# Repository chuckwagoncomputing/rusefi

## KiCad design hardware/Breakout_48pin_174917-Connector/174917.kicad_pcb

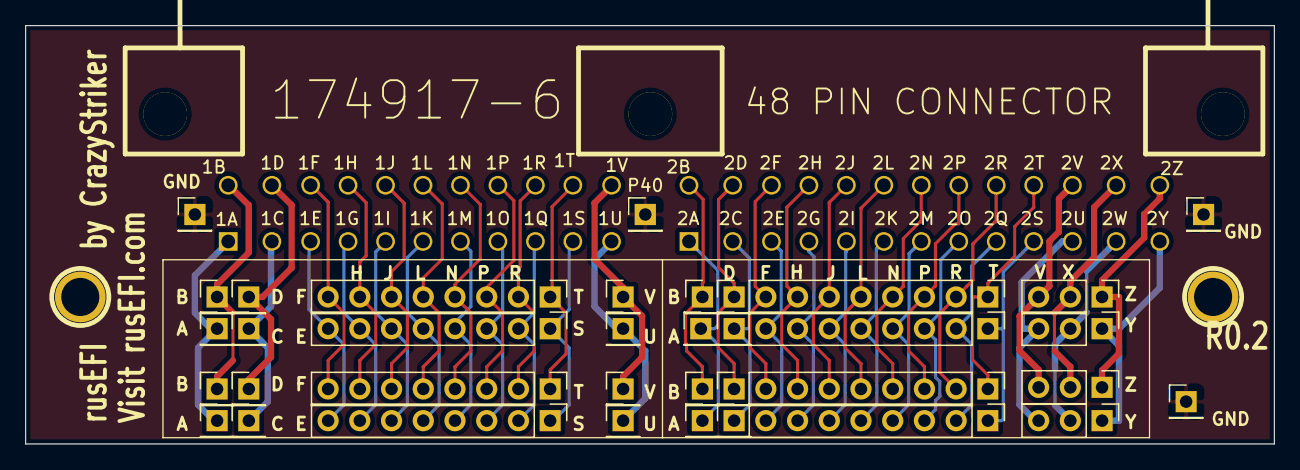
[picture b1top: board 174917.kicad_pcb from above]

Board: 2 copper layers, 100.0 x 33.5 mm, 39 parts (0 on the bottom side), 49 nets.

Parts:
1PIN, 1PIN#2: P***; 1pin
P1, P2, P13, P14: CONN_3; PinHeader_1x03_P2.54mm_Vertical
P3, P4, P5, P6, P7, P8, P9, P10, P11, P12, P15, P16, P17, P18, P19, P20, P21, P22, P23, P24, P38, P39, P40, P41: CONN_1; PinHeader_1x01_P2.54mm_Vertical
P25: 174917
P26, P27, P30, P31, P32, P33, P36, P37: CONN_8; PinHeader_1x08_P2.54mm_Vertical

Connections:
GND: P38.1, P39.1, P40.1, P41.1
unnamed: P1.1, P13.1
unnamed: P1.2, P13.2
unnamed: P1.3, P13.3
unnamed: P10.1, P22.1
unnamed: P11.1, P23.1
unnamed: P12.1, P24.1
unnamed: P2.1, P14.1
unnamed: P2.2, P14.2
unnamed: P2.3, P14.3
unnamed: P3.1, P15.1
unnamed: P4.1, P16.1
unnamed: P5.1, P17.1
unnamed: P6.1, P18.1
unnamed: P7.1, P19.1
unnamed: P8.1, P20.1
unnamed: P9.1, P21.1
unnamed: P26.1, P32.1
unnamed: P26.3, P32.3
unnamed: P26.4, P32.4
unnamed: P26.5, P32.5
unnamed: P26.6, P32.6
unnamed: P26.7, P32.7
unnamed: P26.8, P32.8
unnamed: P27.1, P33.1
unnamed: P27.2, P33.2
unnamed: P27.3, P33.3
unnamed: P27.4, P33.4
unnamed: P27.5, P33.5
unnamed: P27.6, P33.6
unnamed: P27.7, P33.7
unnamed: P27.8, P33.8
unnamed: P30.1, P36.1
unnamed: P30.2, P36.2
unnamed: P30.3, P36.3
unnamed: P30.4, P36.4
unnamed: P30.5, P36.5
unnamed: P30.6, P36.6
unnamed: P30.7, P36.7
unnamed: P30.8, P36.8
unnamed: P31.1, P37.1
unnamed: P31.2, P37.2
unnamed: P31.3, P37.3
unnamed: P31.4, P37.4
unnamed: P31.5, P37.5
unnamed: P31.6, P37.6
unnamed: P31.7, P37.7
unnamed: P31.8, P37.8
unnamed: P26.2, P32.2

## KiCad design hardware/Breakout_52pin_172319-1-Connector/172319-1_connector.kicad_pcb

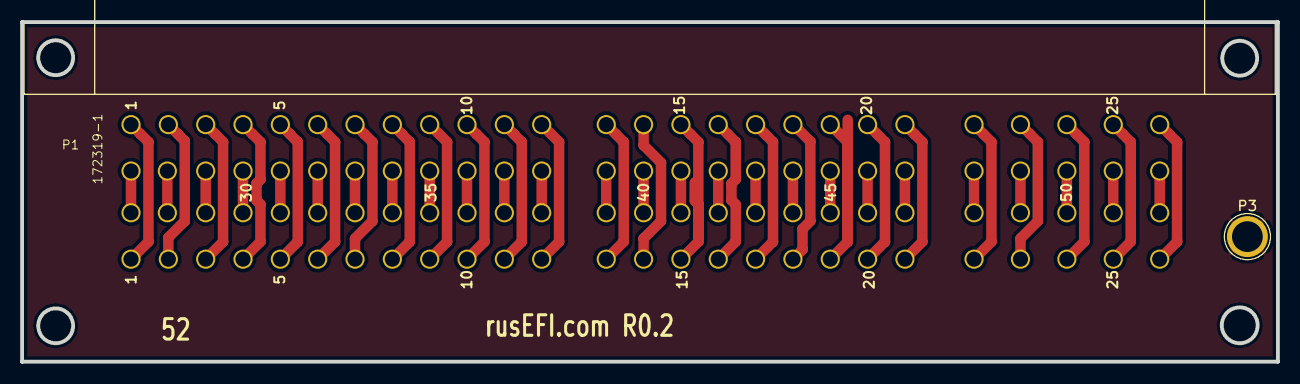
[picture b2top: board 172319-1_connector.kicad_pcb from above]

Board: 2 copper layers, 124.5 x 33.7 mm, 3 parts (1 on the bottom side), 52 nets.

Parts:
P1, P2: 172319-1; 172319-1_connector
P3: CONN_01X01; 1pin

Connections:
unnamed: P1.1, P2.1
unnamed: P1.2, P2.2
unnamed: P1.3, P2.3
unnamed: P1.4, P2.4
unnamed: P1.5, P2.5
unnamed: P1.6, P2.6
unnamed: P1.7, P2.7
unnamed: P1.8, P2.8
unnamed: P1.9, P2.9
unnamed: P1.10, P2.10
unnamed: P1.11, P2.11
unnamed: P1.12, P2.12
unnamed: P1.13, P2.13
unnamed: P1.14, P2.14
unnamed: P1.15, P2.15
unnamed: P1.16, P2.16
unnamed: P1.17, P2.17
unnamed: P1.18, P2.18
unnamed: P1.19, P2.19
unnamed: P1.20, P2.20
unnamed: P1.21, P2.21
unnamed: P1.22, P2.22
unnamed: P1.23, P2.23
unnamed: P1.24, P2.24
unnamed: P1.25, P2.25
unnamed: P1.26, P2.26
unnamed: P1.27, P2.27
unnamed: P1.28, P2.28
unnamed: P1.29, P2.29
unnamed: P1.30, P2.30
unnamed: P1.31, P2.31
unnamed: P1.32, P2.32
unnamed: P1.33, P2.33
unnamed: P1.34, P2.34
unnamed: P1.35, P2.35
unnamed: P1.36, P2.36
unnamed: P1.37, P2.37
unnamed: P1.38, P2.38
unnamed: P1.39, P2.39
unnamed: P1.40, P2.40
unnamed: P1.41, P2.41
unnamed: P1.42, P2.42
unnamed: P1.43, P2.43
unnamed: P1.44, P2.44
unnamed: P1.45, P2.45
unnamed: P1.46, P2.46
unnamed: P1.47, P2.47
unnamed: P1.48, P2.48
unnamed: P1.49, P2.49
unnamed: P1.50, P2.50
unnamed: P1.51, P2.51
unnamed: P1.52, P2.52

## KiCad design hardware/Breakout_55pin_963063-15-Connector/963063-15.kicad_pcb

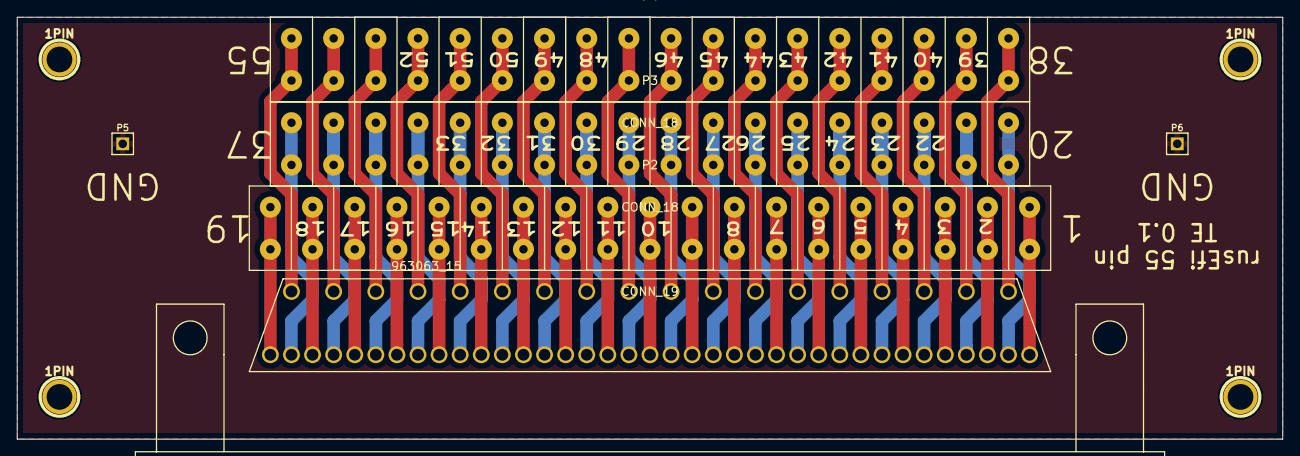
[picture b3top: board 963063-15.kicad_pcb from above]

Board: 2 copper layers, 150.0 x 50.0 mm, 10 parts (0 on the bottom side), 56 nets.

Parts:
1PIN, 1PIN#2, 1PIN#3, 1PIN#4: P***; 1pin
P1: 963063_15; 963063-15
P2: CONN_19; CON19X5
P3, P4: CONN_18; CON18X5
P5, P6: CONN_1; PIN_ARRAY_1

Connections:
GND: P5.1, P6.1
unnamed: P1.11, P2.11
unnamed: P1.1, P2.1
unnamed: P1.2, P2.2
unnamed: P1.3, P2.3
unnamed: P1.4, P2.4
unnamed: P1.5, P2.5
unnamed: P1.6, P2.6
unnamed: P1.7, P2.7
unnamed: P1.8, P2.8
unnamed: P1.9, P2.9
unnamed: P1.10, P2.10
unnamed: P1.55, P4.18
unnamed: P1.12, P2.12
unnamed: P1.13, P2.13
unnamed: P1.14, P2.14
unnamed: P1.15, P2.15
unnamed: P1.16, P2.16
unnamed: P1.17, P2.17
unnamed: P1.18, P2.18
unnamed: P1.19, P2.19
unnamed: P1.20, P3.1
unnamed: P1.21, P3.2
unnamed: P1.44, P4.7
unnamed: P1.34, P3.15
unnamed: P1.35, P3.16
unnamed: P1.36, P3.17
unnamed: P1.37, P3.18
unnamed: P1.38, P4.1
unnamed: P1.39, P4.2
unnamed: P1.40, P4.3
unnamed: P1.41, P4.4
unnamed: P1.42, P4.5
unnamed: P1.43, P4.6
unnamed: P1.22, P3.3
unnamed: P1.45, P4.8
unnamed: P1.46, P4.9
unnamed: P1.47, P4.10
unnamed: P1.48, P4.11
unnamed: P1.49, P4.12
unnamed: P1.50, P4.13
unnamed: P1.51, P4.14
unnamed: P1.52, P4.15
unnamed: P1.53, P4.16
unnamed: P1.54, P4.17
unnamed: P1.33, P3.14
unnamed: P1.23, P3.4
unnamed: P1.24, P3.5
unnamed: P1.25, P3.6
unnamed: P1.26, P3.7
unnamed: P1.27, P3.8
unnamed: P1.28, P3.9
unnamed: P1.29, P3.10
unnamed: P1.30, P3.11
unnamed: P1.31, P3.12
unnamed: P1.32, P3.13

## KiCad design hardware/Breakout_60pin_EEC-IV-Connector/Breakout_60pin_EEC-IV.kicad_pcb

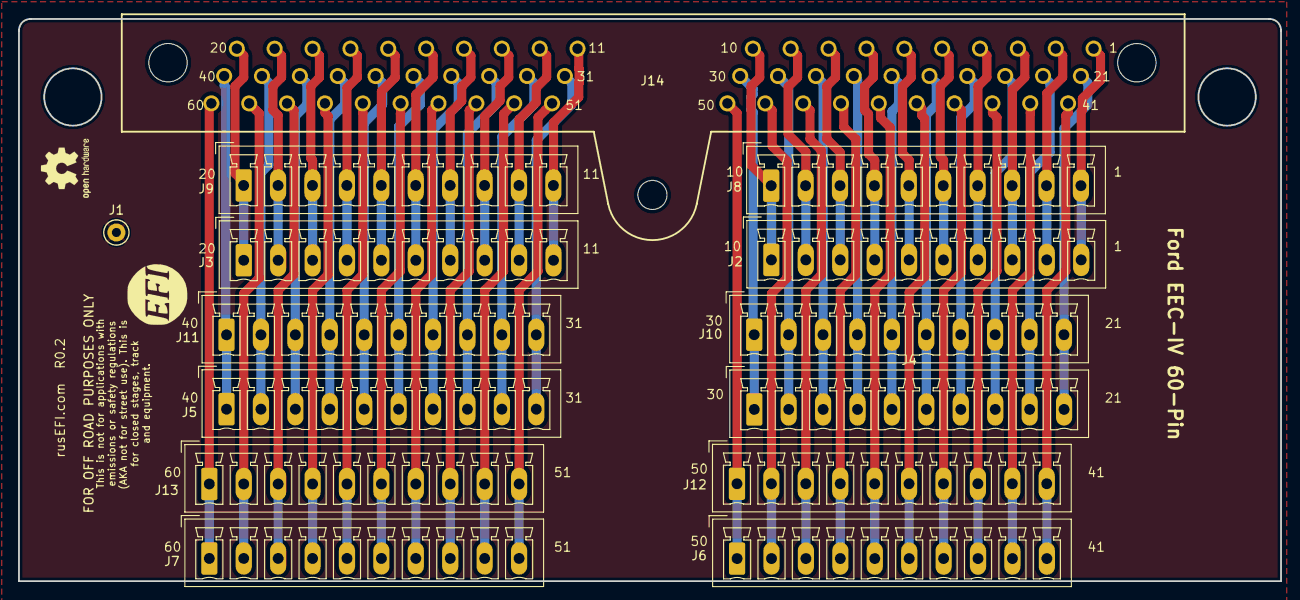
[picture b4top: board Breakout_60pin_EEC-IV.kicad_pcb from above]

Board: 2 copper layers, 139.7 x 62.2 mm, 17 parts (0 on the bottom side), 60 nets.

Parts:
G1: Disclaimer; Off_Road_Disclaimer
G2: LOGO
J1: Conn_01x01; TestPoint_Keystone_5000-5004_Miniature
J2, J3, J4, J5, J6, J7, J8, J9, J10, J11, J12, J13: Conn_01x10; PhoenixContact_MCV_1,5_10-G-3.81_1x10_P3.81mm_Vertical
J14: EEC-IV; eeciv
LOGO1: DNP; OSHW-Logo2_7.3x6mm_SilkScreen

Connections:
/1: J2.10, J8.10, J14.1
/5: J2.6, J8.6, J14.5
/10: J2.1, J8.1, J14.10
/11: J3.10, J9.10, J14.11
/15: J3.6, J9.6, J14.15
/25: J4.6, J10.6, J14.25
/30: J4.1, J10.1, J14.30
/31: J5.10, J11.10, J14.31
/35: J5.6, J11.6, J14.35
/40: J5.1, J11.1, J14.40
/41: J6.10, J12.10, J14.41
/45: J6.6, J12.6, J14.45
/50: J6.1, J12.1, J14.50
/53: J7.8, J13.8, J14.53
/54: J7.7, J13.7, J14.54
/55: J7.6, J13.6, J14.55
/60: J7.1, J13.1, J14.60
/420: J3.1, J9.1, J14.20
/421: J4.10, J10.10, J14.21
unnamed: J4.2, J10.2, J14.29
unnamed: J4.3, J10.3, J14.28
unnamed: J4.4, J10.4, J14.27
unnamed: J4.5, J10.5, J14.26
unnamed: J4.7, J10.7, J14.24
unnamed: J4.8, J10.8, J14.23
unnamed: J4.9, J10.9, J14.22
unnamed: J5.2, J11.2, J14.39
unnamed: J5.3, J11.3, J14.38
unnamed: J5.4, J11.4, J14.37
unnamed: J5.5, J11.5, J14.36
unnamed: J5.7, J11.7, J14.34
unnamed: J5.8, J11.8, J14.33
unnamed: J5.9, J11.9, J14.32
unnamed: J6.2, J12.2, J14.49
unnamed: J6.3, J12.3, J14.48
unnamed: J6.4, J12.4, J14.47
unnamed: J6.5, J12.5, J14.46
unnamed: J6.7, J12.7, J14.44
unnamed: J6.8, J12.8, J14.43
unnamed: J6.9, J12.9, J14.42
unnamed: J7.2, J13.2, J14.59
unnamed: J7.3, J13.3, J14.58
unnamed: J7.4, J13.4, J14.57
unnamed: J7.5, J13.5, J14.56
unnamed: J7.9, J13.9, J14.52
unnamed: J7.10, J13.10, J14.51
unnamed: J2.9, J8.9, J14.2
unnamed: J2.8, J8.8, J14.3
unnamed: J2.7, J8.7, J14.4
unnamed: J2.5, J8.5, J14.6
unnamed: J2.4, J8.4, J14.7
unnamed: J2.3, J8.3, J14.8
unnamed: J2.2, J8.2, J14.9
unnamed: J3.9, J9.9, J14.12
unnamed: J3.8, J9.8, J14.13
unnamed: J3.7, J9.7, J14.14
unnamed: J3.5, J9.5, J14.16
unnamed: J3.4, J9.4, J14.17
unnamed: J3.3, J9.3, J14.18
unnamed: J3.2, J9.2, J14.19

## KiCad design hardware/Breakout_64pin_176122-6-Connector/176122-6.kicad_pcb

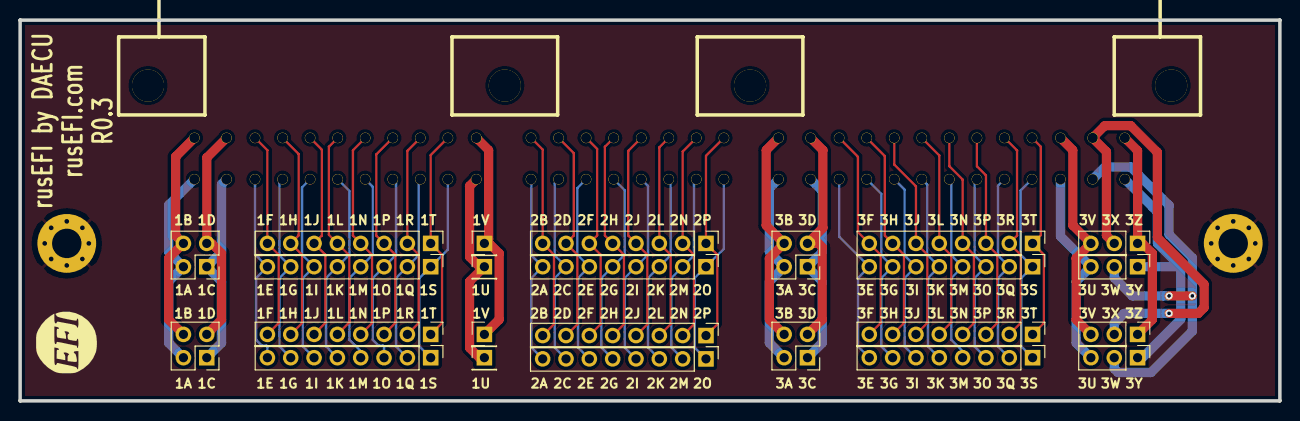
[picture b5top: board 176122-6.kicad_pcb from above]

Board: 2 copper layers, 137.2 x 41.5 mm, 28 parts (0 on the bottom side), 65 nets.

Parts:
G1: LOGO
H1, H2: MountingHole_Pad; MountingHole_3.2mm_M3_Pad_Via
P1, P2, P13, P14: CONN_3; PinHeader_1x03_P2.54mm_Vertical
P3, P4, P42, P43: Conn_01x04_Male; PinHeader_2x02_P2.54mm_Vertical
P7, P8, P19, P20: CONN_1; PinHeader_1x01_P2.54mm_Vertical
P25: 0176122-06; 176122-6
P26, P27, P28, P29, P30, P31, P32, P33, P34, P35, P36, P37: CONN_8; PinHeader_1x08_P2.54mm_Vertical

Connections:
GND: H1.1, H2.1
unnamed: P1.1, P13.1, P25.1
unnamed: P1.2, P13.2, P25.2
unnamed: P1.3, P13.3, P25.3
unnamed: P2.1, P14.1, P25.4
unnamed: P2.2, P14.2, P25.5
unnamed: P2.3, P14.3, P25.6
unnamed: P7.1, P19.1, P25.11
unnamed: P8.1, P20.1, P25.12
unnamed: P3.1, P4.1, P25.7
unnamed: P3.2, P4.2, P25.8
unnamed: P3.3, P4.3, P25.9
unnamed: P3.4, P4.4, P25.10
unnamed: P25.13, P42.1, P43.1
unnamed: P25.14, P42.2, P43.2
unnamed: P25.15, P42.3, P43.3
unnamed: P25.16, P42.4, P43.4
unnamed: P25.17, P26.1, P32.1
unnamed: P25.18, P26.2, P32.2
unnamed: P25.19, P26.3, P32.3
unnamed: P25.20, P26.4, P32.4
unnamed: P25.21, P26.5, P32.5
unnamed: P25.22, P26.6, P32.6
unnamed: P25.23, P26.7, P32.7
unnamed: P25.24, P26.8, P32.8
unnamed: P25.25, P27.1, P33.1
unnamed: P25.26, P27.2, P33.2
unnamed: P25.27, P27.3, P33.3
unnamed: P25.28, P27.4, P33.4
unnamed: P25.29, P27.5, P33.5
unnamed: P25.30, P27.6, P33.6
unnamed: P25.31, P27.7, P33.7
unnamed: P25.32, P27.8, P33.8
unnamed: P25.33, P28.1, P34.1
unnamed: P25.34, P28.2, P34.2
unnamed: P25.35, P28.3, P34.3
unnamed: P25.36, P28.4, P34.4
unnamed: P25.37, P28.5, P34.5
unnamed: P25.38, P28.6, P34.6
unnamed: P25.39, P28.7, P34.7
unnamed: P25.40, P28.8, P34.8
unnamed: P25.41, P29.1, P35.1
unnamed: P25.42, P29.2, P35.2
unnamed: P25.43, P29.3, P35.3
unnamed: P25.44, P29.4, P35.4
unnamed: P25.45, P29.5, P35.5
unnamed: P25.46, P29.6, P35.6
unnamed: P25.47, P29.7, P35.7
unnamed: P25.48, P29.8, P35.8
unnamed: P25.49, P30.1, P36.1
unnamed: P25.50, P30.2, P36.2
unnamed: P25.51, P30.3, P36.3
unnamed: P25.52, P30.4, P36.4
unnamed: P25.53, P30.5, P36.5
unnamed: P25.54, P30.6, P36.6
unnamed: P25.55, P30.7, P36.7
unnamed: P25.56, P30.8, P36.8
unnamed: P25.57, P31.1, P37.1
unnamed: P25.58, P31.2, P37.2
unnamed: P25.59, P31.3, P37.3
unnamed: P25.60, P31.4, P37.4
unnamed: P25.61, P31.5, P37.5
unnamed: P25.62, P31.6, P37.6
unnamed: P25.63, P31.7, P37.7
unnamed: P25.64, P31.8, P37.8

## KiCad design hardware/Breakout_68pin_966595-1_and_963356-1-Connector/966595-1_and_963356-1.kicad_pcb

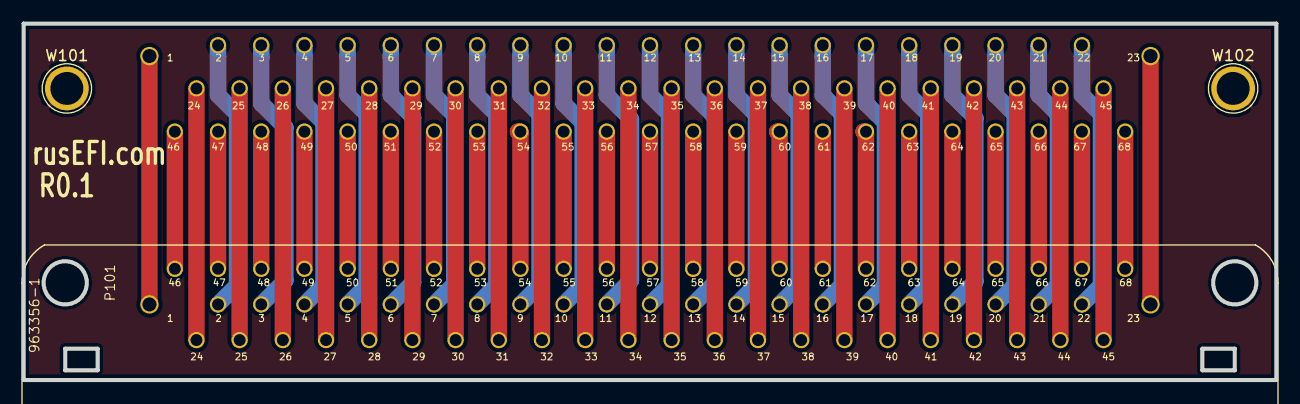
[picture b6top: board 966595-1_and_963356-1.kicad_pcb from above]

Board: 2 copper layers, 116.0 x 33.0 mm, 4 parts (1 on the bottom side), 69 nets.

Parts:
P101: 963356-1
P102: 966595-1
W101, W102: TEST_1P; 1pin

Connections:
GND: W101.1, W102.1
unnamed: P101.1, P102.1
unnamed: P101.2, P102.2
unnamed: P101.3, P102.3
unnamed: P101.4, P102.4
unnamed: P101.5, P102.5
unnamed: P101.6, P102.6
unnamed: P101.7, P102.7
unnamed: P101.8, P102.8
unnamed: P101.9, P102.9
unnamed: P101.10, P102.10
unnamed: P101.11, P102.11
unnamed: P101.12, P102.12
unnamed: P101.13, P102.13
unnamed: P101.14, P102.14
unnamed: P101.15, P102.15
unnamed: P101.16, P102.16
unnamed: P101.17, P102.17
unnamed: P101.18, P102.18
unnamed: P101.19, P102.19
unnamed: P101.20, P102.20
unnamed: P101.21, P102.21
unnamed: P101.22, P102.22
unnamed: P101.23, P102.23
unnamed: P101.24, P102.24
unnamed: P101.25, P102.25
unnamed: P101.26, P102.26
unnamed: P101.27, P102.27
unnamed: P101.28, P102.28
unnamed: P101.29, P102.29
unnamed: P101.30, P102.30
unnamed: P101.31, P102.31
unnamed: P101.32, P102.32
unnamed: P101.33, P102.33
unnamed: P101.34, P102.34
unnamed: P101.35, P102.35
unnamed: P101.36, P102.36
unnamed: P101.37, P102.37
unnamed: P101.38, P102.38
unnamed: P101.39, P102.39
unnamed: P101.40, P102.40
unnamed: P101.41, P102.41
unnamed: P101.42, P102.42
unnamed: P101.43, P102.43
unnamed: P101.44, P102.44
unnamed: P101.45, P102.45
unnamed: P101.46, P102.46
unnamed: P101.47, P102.47
unnamed: P101.48, P102.48
unnamed: P101.49, P102.49
unnamed: P101.50, P102.50
unnamed: P101.51, P102.51
unnamed: P101.52, P102.52
unnamed: P101.53, P102.53
unnamed: P101.54, P102.54
unnamed: P101.55, P102.55
unnamed: P101.56, P102.56
unnamed: P101.57, P102.57
unnamed: P101.58, P102.58
unnamed: P101.59, P102.59
unnamed: P101.60, P102.60
unnamed: P101.61, P102.61
unnamed: P101.62, P102.62
unnamed: P101.63, P102.63
unnamed: P101.64, P102.64
unnamed: P101.65, P102.65
unnamed: P101.66, P102.66
unnamed: P101.67, P102.67
unnamed: P101.68, P102.68

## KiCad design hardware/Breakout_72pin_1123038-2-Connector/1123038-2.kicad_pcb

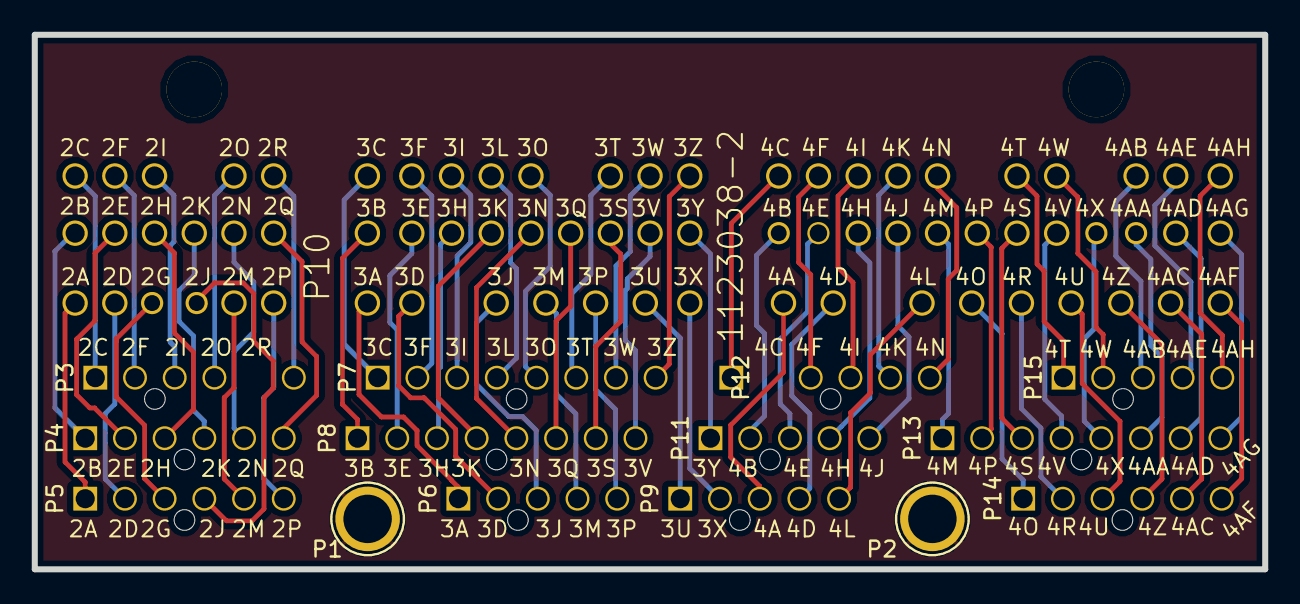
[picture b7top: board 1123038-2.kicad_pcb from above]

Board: 2 copper layers, 77.5 x 33.7 mm, 16 parts (1 on the bottom side), 73 nets.

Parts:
G1: LOGO
P1, P2: CONN_1; 1pin
P3, P6, P9, P11, P12, P15: CONN_01X05; Molex_NanoFit_1x05x2.50mm_Straight
P4, P5, P14: CONN_01X06; Molex_NanoFit_1x06x2.50mm_Straight
P7, P8, P13: CONN_01X08; Molex_NanoFit_1x08x2.50mm_Straight
P10: 1123038-2

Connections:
/2A: P5.1, P10.51
/2B: P4.1, P10.24
/2C: P3.1, P10.1
/2D: P5.2, P10.52
/2E: P4.2, P10.25
/2F: P3.2, P10.2
/2G: P5.3, P10.53
/2H: P4.3, P10.26
/2I: P3.3, P10.3
/2J: P5.4, P10.54
/2K: P4.4, P10.27
/2M: P5.5, P10.55
/2N: P4.5, P10.28
/2P: P5.6, P10.56
/2Q: P4.6, P10.29
/2R: P3.5, P10.5
/3A: P6.1, P10.57
/3B: P8.1, P10.30
/3C: P7.1, P10.6
/3D: P6.2, P10.58
/3E: P8.2, P10.31
/3F: P7.2, P10.7
/3H: P8.3, P10.32
/3I: P7.3, P10.8
/3J: P6.3, P10.59
/3K: P8.4, P10.33
/3L: P7.4, P10.9
/3M: P6.4, P10.60
/3N: P8.5, P10.34
/3O: P7.5, P10.10
/3P: P6.5, P10.61
/3Q: P8.6, P10.35
/3S: P8.7, P10.36
/3T: P7.6, P10.11
/3U: P9.1, P10.62
/3V: P8.8, P10.37
/3W: P7.7, P10.12
/3X: P9.2, P10.63
/3Y: P10.38, P11.1
/3Z: P7.8, P10.13
/4A: P9.3, P10.64
/4AA: P10.48, P13.6
/4AB: P10.21, P15.3
/4AC: P10.71, P14.5
/4AD: P10.49, P13.7
/4AE: P10.22, P15.4
/4AF: P10.72, P14.6
/4AG: P10.50, P13.8
/4AH: P10.23, P15.5
/4B: P10.39, P11.2
/4C: P10.14, P12.1
/4D: P9.4, P10.65
/4E: P10.40, P11.3
/4F: P10.15, P12.2
/4H: P10.41, P11.4
/4I: P10.16, P12.3
/4J: P10.42, P11.5
/4K: P10.17, P12.4
/4L: P9.5, P10.66
/4M: P10.43, P13.1
/4N: P10.18, P12.5
/4O: P10.67, P14.1
/4P: P10.44, P13.2
/4R: P10.68, P14.2
/4S: P10.45, P13.3
/4T: P10.19, P15.1
/4U: P10.69, P14.3
/4V: P10.46, P13.4
/4W: P10.20, P15.2
/4X: P10.47, P13.5
/4Z: P10.70, P14.4
/20: P3.4, P10.4
GND: P1.1, P2.1

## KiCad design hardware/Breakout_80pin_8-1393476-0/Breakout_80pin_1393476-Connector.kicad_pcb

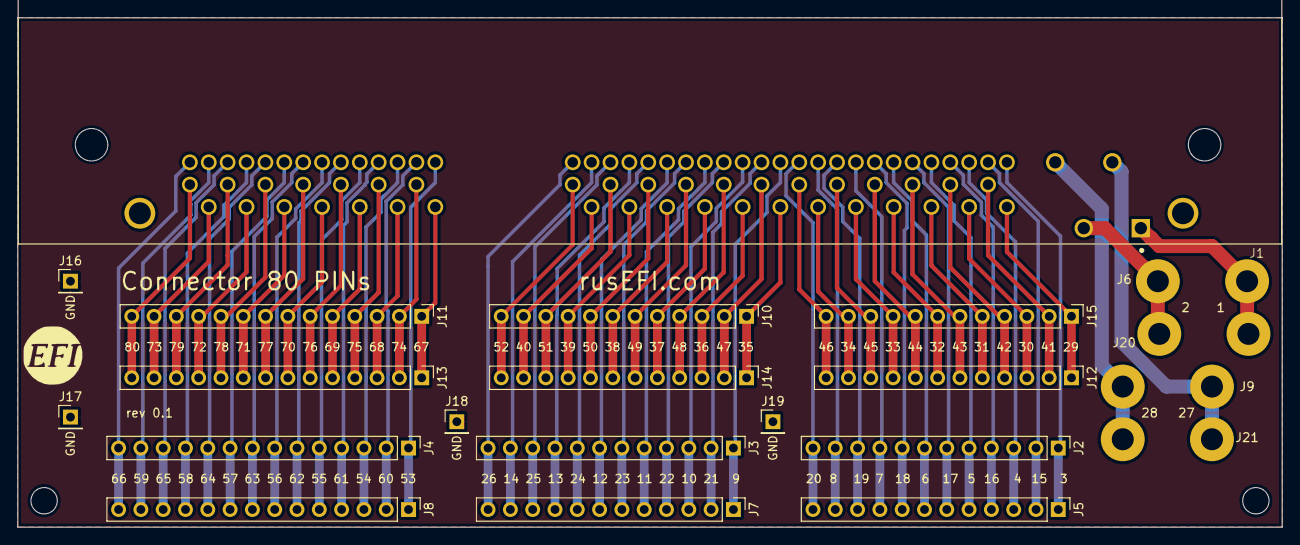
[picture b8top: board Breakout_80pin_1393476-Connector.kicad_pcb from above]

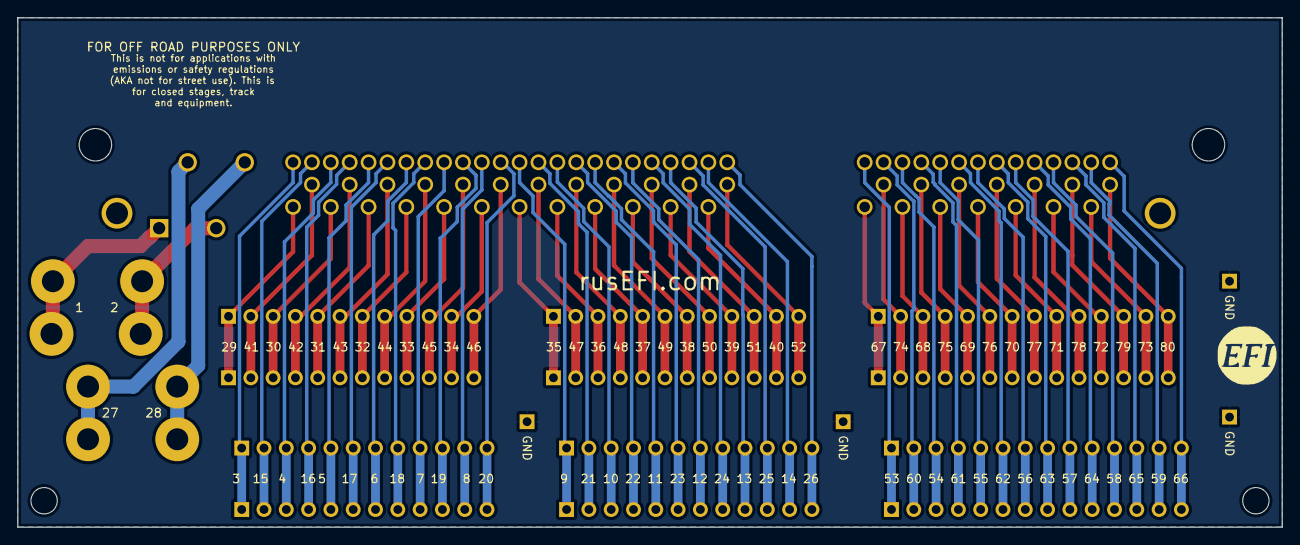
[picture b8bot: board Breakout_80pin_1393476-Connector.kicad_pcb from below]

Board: 2 copper layers, 144.0 x 58.0 mm, 24 parts (2 on the bottom side), 81 nets.

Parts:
G?: LOGO
G?#2: LOGO
G?#3: Disclaimer; Off_Road_Disclaimer
J1: 8-1393476-0
J2, J3, J5, J7, J10, J12, J14, J15: Conn_01x12; Pin_Header_Straight_1x12_Pitch2.54mm
J4, J8, J11, J13: Conn_01x14; Pin_Header_Straight_1x14_Pitch2.54mm
J6, J9, J20, J21: Screw_Terminal_01x02; WireConnection_2.50mmDrill
J16, J17, J18, J19: Conn_01x01; Pin_Header_Straight_1x01_Pitch2.54mm

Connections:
Earth: J1.81, J1.82, J16.1, J17.1, J18.1, J19.1
unnamed: J1.1, J6.1, J20.1
unnamed: J1.2, J6.2, J20.2
unnamed: J1.3, J2.1, J5.1
unnamed: J1.4, J2.3, J5.3
unnamed: J1.5, J2.5, J5.5
unnamed: J1.6, J2.7, J5.7
unnamed: J1.7, J2.9, J5.9
unnamed: J1.8, J2.11, J5.11
unnamed: J1.9, J3.1, J7.1
unnamed: J1.10, J3.3, J7.3
unnamed: J1.11, J3.5, J7.5
unnamed: J1.12, J3.7, J7.7
unnamed: J1.13, J3.9, J7.9
unnamed: J1.14, J3.11, J7.11
unnamed: J1.15, J2.2, J5.2
unnamed: J1.16, J2.4, J5.4
unnamed: J1.17, J2.6, J5.6
unnamed: J1.18, J2.8, J5.8
unnamed: J1.19, J2.10, J5.10
unnamed: J1.20, J2.12, J5.12
unnamed: J1.21, J3.2, J7.2
unnamed: J1.22, J3.4, J7.4
unnamed: J1.23, J3.6, J7.6
unnamed: J1.24, J3.8, J7.8
unnamed: J1.25, J3.10, J7.10
unnamed: J1.26, J3.12, J7.12
unnamed: J1.27, J9.1, J21.1
unnamed: J1.28, J9.2, J21.2
unnamed: J1.29, J12.1, J15.1
unnamed: J1.30, J12.3, J15.3
unnamed: J1.31, J12.5, J15.5
unnamed: J1.32, J12.7, J15.7
unnamed: J1.33, J12.9, J15.9
unnamed: J1.34, J12.11, J15.11
unnamed: J1.35, J10.1, J14.1
unnamed: J1.36, J10.3, J14.3
unnamed: J1.37, J10.5, J14.5
unnamed: J1.38, J10.7, J14.7
unnamed: J1.39, J10.9, J14.9
unnamed: J1.40, J10.11, J14.11
unnamed: J1.41, J12.2, J15.2
unnamed: J1.42, J12.4, J15.4
unnamed: J1.43, J12.6, J15.6
unnamed: J1.44, J12.8, J15.8
unnamed: J1.45, J12.10, J15.10
unnamed: J1.46, J12.12, J15.12
unnamed: J1.47, J10.2, J14.2
unnamed: J1.48, J10.4, J14.4
unnamed: J1.49, J10.6, J14.6
unnamed: J1.50, J10.8, J14.8
unnamed: J1.51, J10.10, J14.10
unnamed: J1.52, J10.12, J14.12
unnamed: J1.53, J4.1, J8.1
unnamed: J1.54, J4.3, J8.3
unnamed: J1.55, J4.5, J8.5
unnamed: J1.56, J4.7, J8.7
unnamed: J1.57, J4.9, J8.9
unnamed: J1.58, J4.11, J8.11
unnamed: J1.59, J4.13, J8.13
unnamed: J1.60, J4.2, J8.2
unnamed: J1.61, J4.4, J8.4
unnamed: J1.62, J4.6, J8.6
unnamed: J1.63, J4.8, J8.8
unnamed: J1.64, J4.10, J8.10
unnamed: J1.65, J4.12, J8.12
unnamed: J1.66, J4.14, J8.14
unnamed: J1.67, J11.1, J13.1
unnamed: J1.68, J11.3, J13.3
unnamed: J1.69, J11.5, J13.5
unnamed: J1.70, J11.7, J13.7
unnamed: J1.71, J11.9, J13.9
unnamed: J1.72, J11.11, J13.11
unnamed: J1.73, J11.13, J13.13
unnamed: J1.74, J11.2, J13.2
unnamed: J1.75, J11.4, J13.4
unnamed: J1.76, J11.6, J13.6
unnamed: J1.77, J11.8, J13.8
unnamed: J1.78, J11.10, J13.10
unnamed: J1.79, J11.12, J13.12
unnamed: J1.80, J11.14, J13.14
